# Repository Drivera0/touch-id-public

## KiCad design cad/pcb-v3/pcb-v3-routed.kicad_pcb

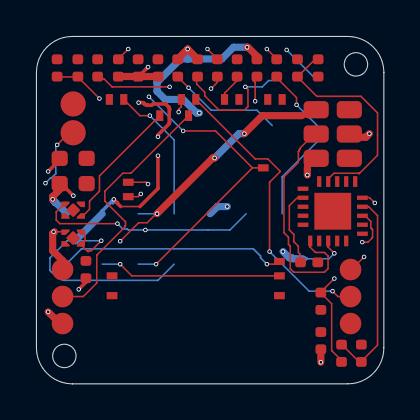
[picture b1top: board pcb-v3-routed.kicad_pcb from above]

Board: 4 copper layers, 19.3 x 19.3 mm, 44 parts (0 on the bottom side), 27 nets.

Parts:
BT1: BT1
C1: C1
C2: C2
C3: C3
C4: C4
C5: C5
C6: C6
C7: C7
C8: C8
C9: C9
C10: C10
C12: C12
C13: C13
J2: J2
J3: J3
J4: J4
J11: J11
L1: L1
R1: R1
R2: R2
R3: R3
R4: R4
R5: R5
R6: R6
R7: R7
ROK1: ROK1
ROK2: ROK2
ROK3: ROK3
ROV1: ROV1
ROV2: ROV2
TP1: TP1
TP2: TP2
TP3: TP3
TP4: TP4
TP5: TP5
TP6: TP6
TP7: TP7
TP8: TP8
TP9: TP9
TP10: TP10
U1: U1
U2: U2
U3: U3
U4: U4

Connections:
BL_FLAG: C13.1, R6.2, U1.11
BL_RETURN: J11.4, R6.1, TP7.1
GND: BT1.2, C1.2, C2.2, C3.2, C4.2, C5.2, C6.2, C7.2, C8.2, C9.2, C10.2, C12.2, C13.2, J2.6, J3.5, J4.5, R5.2, ROK1.2, ROV1.2, TP8.1, TP9.1, TP10.1, U1.1, U1.2, U1.15, U1.32, U1.33, U1.55, U2.1, U2.3, U2.5, U2.6, U2.15, U2.16, U2.17, U2.21, U3.2, U3.5, U4.2, U4.5
HARV_1: J11.1, R1.1
HARV_2: J11.2, R2.1
HARV_3: J11.3, R3.1
LX: L1.1, U2.20
NRF_VDD: C9.1, U1.28
OK_HYST: ROK2.1, ROK3.2, U2.11
OK_PROG: ROK1.1, ROK2.2, U2.12
RESET: J3.3, R7.2, U1.40
SENSOR_3V3: C6.1, C7.1, J2.1, TP5.1, U3.1
SENSOR_MCU_3V3: C8.1, J2.3, TP6.1, U4.1
SENSOR_RX: J2.5, U1.24
SENSOR_SW_EN: U1.19, U4.3
SENSOR_TX: J2.4, U1.22
SENSOR_WAKEUP: J2.2, U1.23
SWCLK: J3.2, U1.53
SWDIO: J3.1, U1.51
VBAT: BT1.1, C5.1, TP3.1, U2.18
VBAT_OK: R7.1, TP4.1, U1.16, U2.13
VBAT_OV_SET: ROV1.1, ROV2.2, U2.7
VBAT_SENSE: C12.1, R4.2, R5.1, U1.9
VIN_DC: C1.1, L1.2, R1.2, R2.2, R3.2, TP1.1, U2.2
VRDIV: ROK3.1, ROV2.1, U2.8
VREF_SAMP: C4.1, U2.4
VSTOR: C2.1, C3.1, C10.1, J3.4, R4.1, TP2.1, U1.30, U2.19, U3.3, U3.4, U4.4

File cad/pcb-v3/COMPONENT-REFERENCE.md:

---
title: Component reference — datasheets, models, and what is already verified
type: project
updated: 2026-08-29
---

# Component reference

**One index for every part on the board**, so nobody has to re-derive a part
number or go hunting for a datasheet again.

> [!important] **Most of this does NOT need downloading.**
> Every footprint on `pcb-v3-handoff.kicad_pcb` has **already been measured
> against its package** by `verify_sourcing.py` (it compares each land to the
> part actually bought, using rotated pad corners rather than circumscribed
> circles). `preflight.py` re-checks the whole board before any order.
>
> **So the only part that needs a new footprint is the PCM.** Pulling 3D models
> for the passives would be work without a purpose — they are 0402s and 0603s
> whose lands are verified and whose height (0.5 mm) is nowhere near the 2.25 mm
> cell seat.

## The board — 20 distinct parts

| refs | part | LCSC | lib | JLC stock | datasheet |
|---|---|---|---|---|---|
| U1 | Raytac MDBT50Q-1MV2, SMD-61P | `C5118826` | extended | 0 | [PDF](https://www.lcsc.com/datasheet/C5118826.pdf) |
| U2 | TI BQ25505RGRR, VQFN-20-EP 3.5x3.5 | `C882746` | extended | 829 | [PDF](https://www.lcsc.com/datasheet/C882746.pdf) |
| U3, U4 | TI TPS7A2033DQNR, X2SON-4 1x1 | `C46459900` | extended | 4371 | [PDF](https://www.lcsc.com/datasheet/C46459900.pdf) |
| L1 | DMBJ PNLS252012-220M 22uH, 1008, 1.02R, 500mA | `C2849435` | extended | 2288 | [PDF](https://www.lcsc.com/datasheet/C2849435.pdf) |
| C1, C2 | Murata GRM155R61A106ME44D 10uF 10V X5R 0402 | `C77000` | extended | 543698 | [PDF](https://www.lcsc.com/datasheet/C77000.pdf) |
| C5 | FH 0603X106K160NT 10uF 16V X5R 0603 | `C70225` | extended | 479335 | [PDF](https://www.lcsc.com/datasheet/C70225.pdf) |
| C7 | CCTC TCC0603X5R226M100CT 22uF 10V X5R 0603 | `C20416425` | extended | 1168621 | [PDF](https://www.lcsc.com/datasheet/C20416425.pdf) |
| C4 | Murata GRM1555C1H103JE01D 10nF 50V C0G 0402 | `C22400107` | extended | 72632 | [PDF](https://www.lcsc.com/datasheet/C22400107.pdf) |
| C10, C3 | Samsung CL05B104KO5NNNC 100nF 16V X7R 0402 | `C1525` | BASIC | 35834447 | [PDF](https://www.lcsc.com/datasheet/C1525.pdf) |
| C6, C8, C9 | Samsung CL05A105KA5NQNC 1uF 25V X5R 0402 | `C52923` | BASIC | 11865003 | [PDF](https://www.lcsc.com/datasheet/C52923.pdf) |
| C12, C13 | Samsung CL05B103KB5NNNC 10nF 50V X7R 0402 | `C15195` | BASIC | 8405016 | [PDF](https://www.lcsc.com/datasheet/C15195.pdf) |
| R1, R2, R3, R7 | UNI-ROYAL 0402WGF1001TCE 1k 1% 0402 | `C11702` | BASIC | 13920787 | [PDF](https://www.lcsc.com/datasheet/C11702.pdf) |
| R4 | FOJAN FRC0402F4704TS 4.7M 1% 0402 | `C3013173` | extended | 263891 | [PDF](https://www.lcsc.com/datasheet/C3013173.pdf) |
| R5 | UNI-ROYAL 0402WGF1004TCE 1M 1% 0402 | `C26083` | BASIC | 3470670 | [PDF](https://www.lcsc.com/datasheet/C26083.pdf) |
| R6 | UNI-ROYAL 0402WGF1003TCE 100k 1% 0402 | `C25741` | BASIC | 14849306 | [PDF](https://www.lcsc.com/datasheet/C25741.pdf) |
| ROK1 | YAGEO RC0402FR-074M53L 4.53M 1% 0402 | `C137964` | extended | 9229 | [PDF](https://www.lcsc.com/datasheet/C137964.pdf) |
| ROK2 | YAGEO RC0402FR-077M15L 7.15M 1% 0402 | `C477783` | extended | 4637 | [PDF](https://www.lcsc.com/datasheet/C477783.pdf) |
| ROK3 | FOJAN FRC0402F1334TS 1.33M 1% 0402 | `C5713265` | extended | 103945 | [PDF](https://www.lcsc.com/datasheet/C5713265.pdf) |
| ROV1 | Walsin WR04W6044FTL 6.04M 1% 0402 | `C172106` | extended | 2040 | [PDF](https://www.lcsc.com/datasheet/C172106.pdf) |
| ROV2 | YAGEO RC0402FR-076M98L 6.98M 1% 0402 | `C137942` | extended | 2674 | [PDF](https://www.lcsc.com/datasheet/C137942.pdf) |
LCSC datasheet links resolve for every code above. JLC assembly stock is a
**2026-08-28 snapshot** — re-check at order time (preflight WARN 21b).

## The three parts that are NOT on the BOM

These are hand-fitted, so they never appear in the assembly files.

| what | part | datasheet | status |
|---|---|---|---|
| Fingerprint sensor | **HLK-ZW0922** | `datasheets/HLK-ZW0922 Specification V1.0_2024-11-20.pdf` + rendered drawing | **archived here** |
| Cell | bare 1254-class + factory leads | see `CELL-DECIDED.md` | awaiting choice |
| **PCM (new)** | **Mitsumi MC3651DF1AAM** | `datasheets/MC3651_SeriesSpecifications.pdf` + rendered bottom view | **archived here** |

## Where to buy the two that JLC cannot supply today

| part | source | price | note |
|---|---|---|---|
| **U1** MDBT50Q-1MV2 | consign to JLC | — | JLC stock 0; customer ships to their warehouse |
| **PCM** MC3651DF1AAM | **Digi-Key CA `2508-MC3651DF1AAMCT-ND`** | **US$1.33 @ qty 1** | **Active, 2,485 in stock, Cut Tape** |

## CAD / 3D models — what actually exists

| part | model? | where |
|---|---|---|
| **MC3651DF1AAM** | **YES — Ultra Librarian, symbol + footprint** | `digikey.ca/en/models/13684190?tab=ultralibrarian` |
| AP6683 (rejected alt) | yes — EasyEDA symbol + footprint | JLC part page `C2849565` |
| everything else on the BOM | **not needed** | lands already verified on the board |

## Files archived in `datasheets/`

* `MC3651_SeriesSpecifications.pdf` — the PCM, 8 pages, full electricals
* `MC3651-PLP-4E-bottom-view.png` — 600 dpi render of the terminal geometry
* `HLK-ZW0922 Specification V1.0_2024-11-20.pdf` — the sensor
* `ZW0922-dimensions-drawing.png` — 260 dpi render of §2.3

> [!warning] **Downloads land where I cannot reach them.**
> Anything downloaded through the browser goes to the machine's Downloads
> folder. This session can only see the vault, the uploads folder and its own
> scratch space. **To get a file to me, drop it in the vault or attach it to a
> message** — that is how the ZW0922 spec and this PCM datasheet arrived, and
> both worked first time.

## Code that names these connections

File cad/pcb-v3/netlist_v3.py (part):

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part("U4", "TI TPS7A2033 3.3 V LDO (switched sensor-MCU rail)", 5, {
    1: "SENSOR_MCU_3V3", # OUT
    2: "GND",
    3: "SENSOR_SW_EN",   # EN — logic level, driven by an nRF GPIO
    4: "VSTOR",          # IN — from the cell rail, NOT cascaded off U3
    5: "GND",            # thermal
}, "Fed from VSTOR rather than cascaded off SENSOR_3V3: cascading would "
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
# harvest current limiting — also what isolates the three channels,
# which is why no ORing diodes are needed
rc("R1", "1k 0201", "HARV_1", "VIN_DC", "caps awake draw to ~1.1 mA/pin")
rc("R2", "1k 0201", "HARV_2", "VIN_DC")
rc("R3", "1k 0201", "HARV_3", "VIN_DC")

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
